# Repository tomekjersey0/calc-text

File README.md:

# CalcText

## What is CalcText?

CalcText is a wireless messaging device enclosed inside a scientific calculator, powered by a single AAA battery. Two units can message each other directly over LoRa, not requiring Wi-Fi, mobile data, or any kind of external infrastructure. The idea came to me from wanting to message a friend who sat far away from me in my maths class without using my phone or shouting. Despite being a little odd, the idea stuck with me.

*CalcText Rev A mainboard 3D render.*

## How it works

CalcText replaces all of the internal calculator electronics, including the PCB and LCD screen, whilst making use of some of the existing mechanical features.

CalcText makes use of several electronic components.

| Part | Purpose |
| --- | --- |
| Wio-E5-LE | MCU and LoRa radio module |
| TPS61299 | Boosts AAA voltage to 3.3 V |
| PCAL9535A | GPIO expander, scans original keypad matrix for input |
| HLCD290TB reflective display | Replacement display for calculator |
| Interposer board | Connects display to mainboard |
| ~90 mm wire antenna | Used for 868 MHz LoRa |

*Original calculator keypad and PCB assembly.*

CalcText makes use of an existing elastomeric keypad that was part of the original calculator. It gives the user a way to interact with the contacts on the PCB. The old contact pattern is therefore replicated on the replacement PCB.

*Rev A mainboard PCB layout.*

A direct FPC connection isn't viable from the reflective display to the mainboard, so an intermediary interposer board is used, to be located on the rear of the display.

*LCD interposer 3D render.*

## Fitting it inside the calculator

The main challenge is getting everything to fit inside the original enclosure.

| Part to fit | Issue | Resolution |
| --- | --- | --- |
| Mainboard | There are mounting holes, thickness, and outline constraints | Produced acrylic fit test using school equipment and measured original PCB thickness with calipers |
| Display | Larger footprint and thinner than original | Sections of the enclosure can be removed, and PORON foam can secure it |
| Interposer | Unknown FPC landing position due to bend once display is installed | Order screen first and design interposer size based on measured landing position |
| Antenna | Needs sufficient distance from metal and components to ensure good transmission quality | Keep antenna routed down long edge through visible gap, allow it to exit the PCB as far from the display and battery as possible |

*Acrylic mainboard fit test inside the calculator enclosure + Location of battery.*

## Current status

| Element | Status |
| --- | --- |
| Mainboard schematic | Complete |
| Mainboard layout | Complete |
| Interposer schematic | Complete |
| Interposer layout | Pending display measurements |
| BOM | Complete |
| Physical build | Pending components |
| Funding | Pending review |

## Next steps

1. Submit project for review
2. Order all currently finalised parts
3. Take necessary measurements
4. Complete and order interposer
5. Fully assemble 2 CalcTexts
6. Write firmware
7. Test messaging
8. Tune antenna if necessary
9. Project complete

## BOM

The full BOM can be found in [`bom.csv`](bom.csv).
This BOM covers *two* individual CalcText units.

## Credits

This project was enabled by [Hack Club, Macondo](https://macondo.hackclub.com).

You can access the project's full development journal [here](https://macondo.hackclub.com/projects/16515).

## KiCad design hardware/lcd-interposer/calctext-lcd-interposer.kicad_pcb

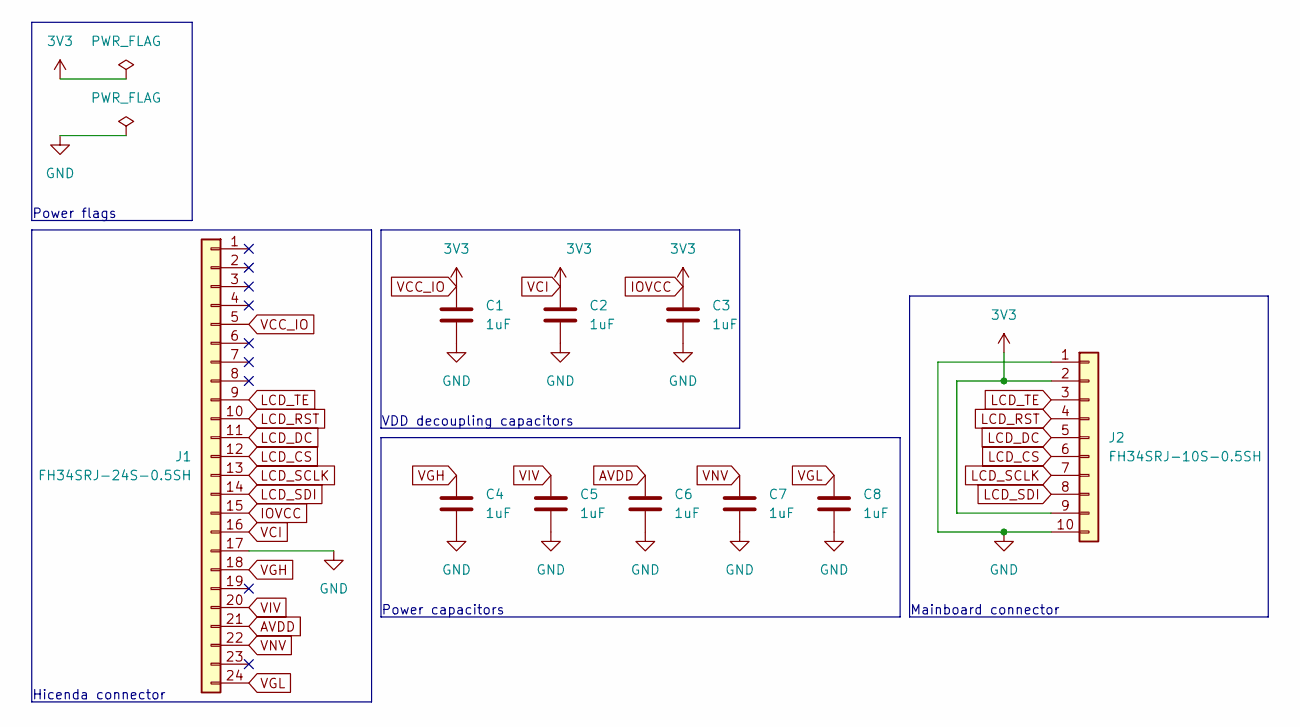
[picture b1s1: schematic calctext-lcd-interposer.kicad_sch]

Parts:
C1, C2, C3, C4, C5, C6, C7, C8: 1uF; C_0402_1005Metric; MPN C1005X5R1E105K050BC
J1: FH34SRJ-24S-0.5SH; Hirose_FH34SRJ-24S-0.5SH; MPN FH34SRJ-24S-0.5SH(99)
J2: FH34SRJ-10S-0.5SH; Hirose_FH34SRJ-10S-0.5SH; MPN FH34SRJ-10S-0.5SH(99)

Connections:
AVDD: C6.2, J1.21
GND: C1.1, C2.1, C3.1, C4.1, C5.1, C6.1, C7.1, C8.1, J1.17, J2.1 (3.3V), J2.10 (GND_P)
IOVCC: C1.2, C2.2, C3.2, J1.5, J1.15, J1.16, J2.2 (GND_L), J2.9 (VBIAS)
LCD_CS: J1.12, J2.6 (DC)
LCD_DC: J1.11, J2.5 (NSS)
LCD_RST: J1.10, J2.4 (MOSI)
LCD_SCLK: J1.13, J2.7 (RESET)
LCD_SDI: J1.14, J2.8 (PWM)
LCD_TE: J1.9, J2.3 (SCK)
VGH: C4.2, J1.18
VGL: C8.2, J1.24
VIV: C5.2, J1.20
VNV: C7.2, J1.22

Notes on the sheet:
VDD decoupling capacitors
Hicenda connector
Power capacitors
Mainboard connector
Power flags

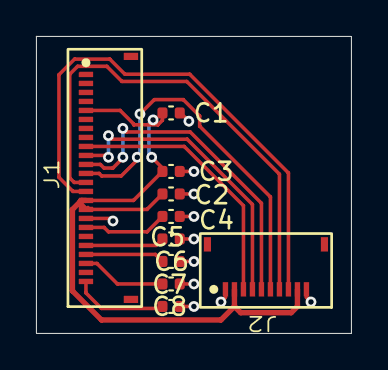
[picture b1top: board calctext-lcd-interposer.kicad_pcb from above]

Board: 2 copper layers, 17.5 x 16.5 mm, 10 parts (0 on the bottom side), 13 nets.

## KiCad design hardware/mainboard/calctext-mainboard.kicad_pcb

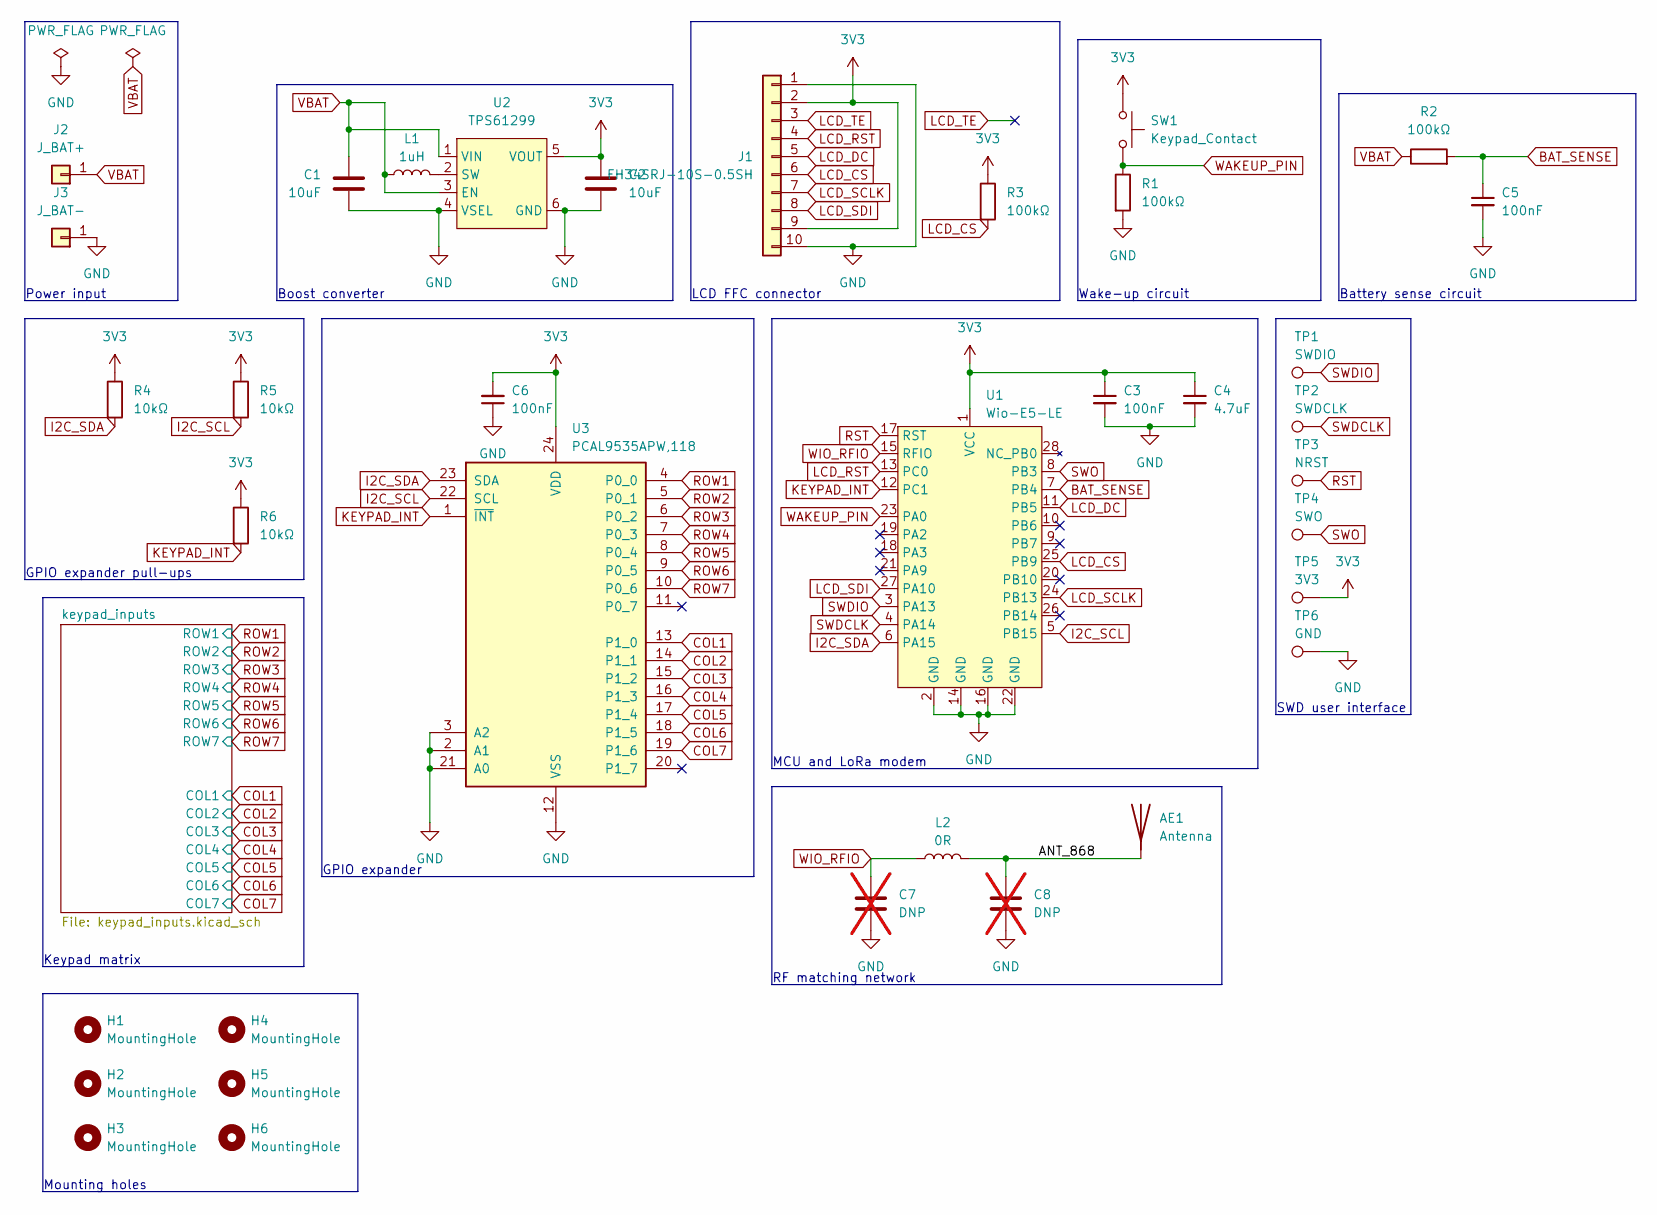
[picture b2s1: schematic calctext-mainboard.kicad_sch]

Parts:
AE1: Antenna; Wire_Antenna_PTH
C1, C2: 10uF; C_0805_2012Metric_Pad1.18x1.45mm_HandSolder; MPN CL21B106KOQNNNE
C3, C5, C6: 100nF; C_0603_1608Metric_Pad1.08x0.95mm_HandSolder; MPN C0603C104K5RACTU
C4: 4.7uF; C_0603_1608Metric_Pad1.08x0.95mm_HandSolder; MPN CL10B475KQ8NNNC
C7, C8: DNP; C_0402_1005Metric; not fitted
H1, H2, H3, H4, H5, H6: MountingHole; MountingHole_4.3mm_M4
J1: FH34SRJ-10S-0.5SH; Hirose_FH34SRJ-10S-0.5SH; MPN FH34SRJ-10S-0.5SH(99)
J2: J_BAT+; Wire_Solder_PTH
J3: J_BAT-; Wire_Solder_PTH
L1: 1uH; L_INPAQ_WIP252010; MPN WIP252010P-1R0ML
L2: 0R; L_0402_1005Metric; MPN RC0402JR-070RL
R1, R2, R3: 100kΩ; R_0603_1608Metric_Pad0.98x0.95mm_HandSolder; MPN RMCF0603FT100K
R4, R5, R6: 10kΩ; R_0603_1608Metric_Pad0.98x0.95mm_HandSolder; MPN RC0603FR-0710KL
SW1: Keypad_Contact
TP1: SWDIO; TestPoint_Pad_D2.0mm
TP2: SWDCLK; TestPoint_Pad_D2.0mm
TP3: NRST; TestPoint_Pad_D2.0mm
TP4: SWO; TestPoint_Pad_D2.0mm
TP5: 3V3; TestPoint_Pad_D2.0mm
TP6: GND; TestPoint_Pad_D2.0mm
U1: Wio-E5-LE; MPN Wio-E5-LE
U2: TPS61299; Texas_R-PDSO-N6_DRL-6; MPN TPS61299DRLR
U3: PCAL9535APW,118; TSSOP-24_4.4x7.8mm_P0.65mm; MPN PCAL9535APW,118

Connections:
3V3: C2.1, C3.1, C4.1, C6.2, J1.2 (GND_L), J1.9 (VBIAS), R3.1, R4.1, R5.1, R6.1, SW1.1, TP5.1, U1.1 (VCC), U2.5 (VOUT), U3.24 (VDD)
/ANT_868: AE1.1 (A), C8.1, L2.2
BAT_SENSE: C5.1, R2.2, U1.7 (PB4)
COL1: U3.13 (P1_0); also elsewhere on the board
COL2: U3.14 (P1_1); also elsewhere on the board
COL3: U3.15 (P1_2); also elsewhere on the board
COL4: U3.16 (P1_3); also elsewhere on the board
COL5: U3.17 (P1_4); also elsewhere on the board
COL6: U3.18 (P1_5); also elsewhere on the board
COL7: U3.19 (P1_6); also elsewhere on the board
GND: C1.2, C2.2, C3.2, C4.2, C5.2, C6.1, C7.2, C8.2, J1.1 (3.3V), J1.10 (GND_P), J3.1, R1.2, TP6.1, U1.2 (GND), U1.14 (GND), U1.16 (GND), U1.22 (GND), U2.4 (VSEL), U2.6 (GND), U3.2 (A1), U3.3 (A2), U3.12 (VSS), U3.21 (A0)
I2C_SCL: R5.2, U1.5 (PB15), U3.22 (SCL)
I2C_SDA: R4.2, U1.6 (PA15), U3.23 (SDA)
KEYPAD_INT: R6.2, U1.12 (PC1), U3.1 (~INT)
LCD_CS: J1.6 (DC), R3.2, U1.25 (PB9)
LCD_DC: J1.5 (NSS), U1.11 (PB5)
LCD_RST: J1.4 (MOSI), U1.13 (PC0)
LCD_SCLK: J1.7 (RESET), U1.24 (PB13)
LCD_SDI: J1.8 (PWM), U1.27 (PA10)
LCD_TE: J1.3 (SCK)
unnamed: L1.2, U2.2 (SW)
ROW1: U3.4 (P0_0); also elsewhere on the board
ROW2: U3.5 (P0_1); also elsewhere on the board
ROW3: U3.6 (P0_2); also elsewhere on the board
ROW4: U3.7 (P0_3); also elsewhere on the board
ROW5: U3.8 (P0_4); also elsewhere on the board
ROW6: U3.9 (P0_5); also elsewhere on the board
ROW7: U3.10 (P0_6); also elsewhere on the board
RST: TP3.1, U1.17 (RST)
SWDCLK: TP2.1, U1.4 (PA14)
SWDIO: TP1.1, U1.3 (PA13)
SWO: TP4.1, U1.8 (PB3)
VBAT: C1.1, J2.1, L1.1, R2.1, U2.1 (VIN), U2.3 (EN)
WAKEUP_PIN: R1.1, SW1.2, U1.23 (PA0)
WIO_RFIO: C7.1, L2.1, U1.15 (RFIO)

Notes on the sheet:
Keypad matrix
Wake-up circuit
Power input
GPIO expander pull-ups
Boost converter
MCU and LoRa modem
GPIO expander
LCD FFC connector
SWD user interface
RF matching network
Mounting holes
Battery sense circuit

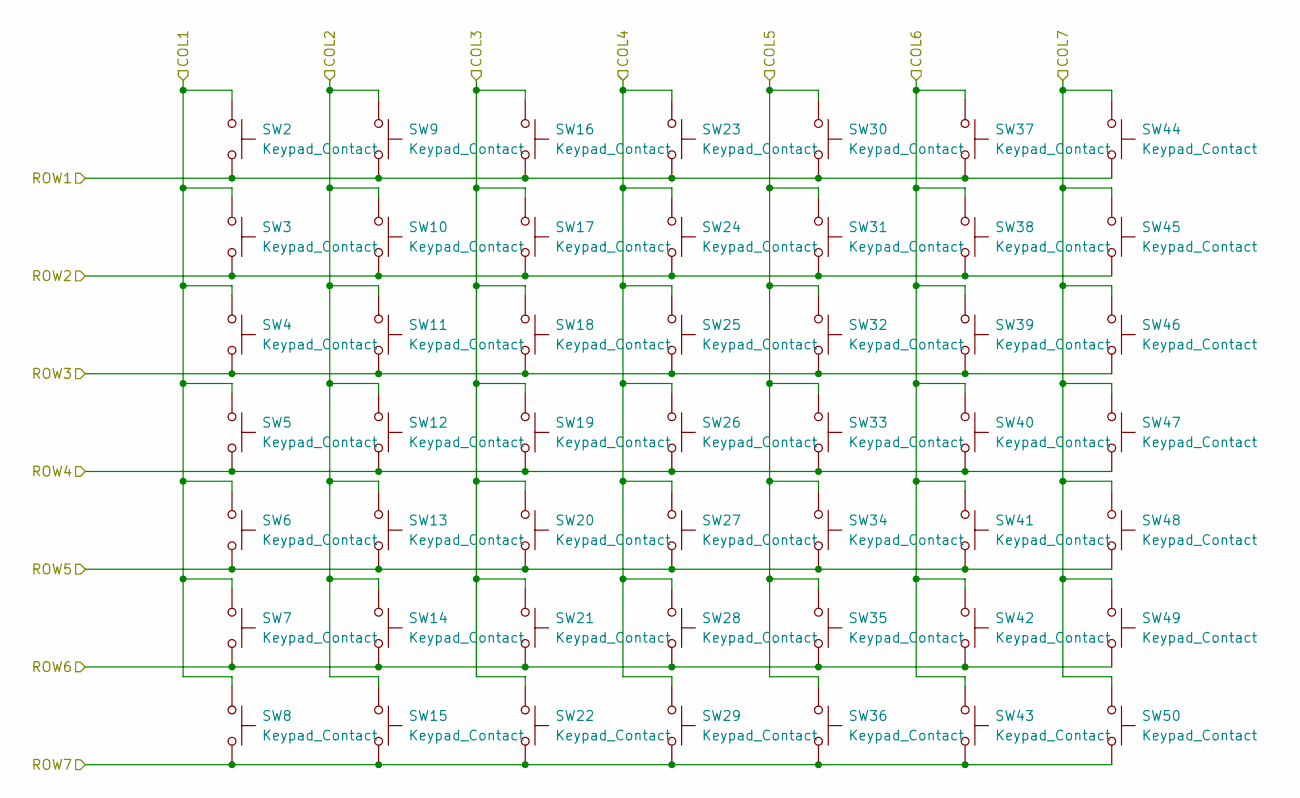
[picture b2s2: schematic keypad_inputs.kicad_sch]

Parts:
SW2, SW3, SW4, SW5, SW6, SW7, SW8, SW9, SW10, SW11, SW12, SW13, SW14, SW15, SW16, SW17, SW18, SW19, SW20, SW21, SW22, SW23, SW24, SW25, SW26, SW27, SW28, SW29, SW30, SW31, SW32, SW33, SW34, SW35, SW36, SW37, SW38, SW39, SW40, SW41, SW42, SW43, SW44, SW45, SW46, SW47, SW48, SW49, SW50: Keypad_Contact

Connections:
COL1: SW2.1, SW3.1, SW4.1, SW5.1, SW6.1, SW7.1, SW8.1; also elsewhere on the board
COL2: SW9.1, SW10.1, SW11.1, SW12.1, SW13.1, SW14.1, SW15.1; also elsewhere on the board
COL3: SW16.1, SW17.1, SW18.1, SW19.1, SW20.1, SW21.1, SW22.1; also elsewhere on the board
COL4: SW23.1, SW24.1, SW25.1, SW26.1, SW27.1, SW28.1, SW29.1; also elsewhere on the board
COL5: SW30.1, SW31.1, SW32.1, SW33.1, SW34.1, SW35.1, SW36.1; also elsewhere on the board
COL6: SW37.1, SW38.1, SW39.1, SW40.1, SW41.1, SW42.1, SW43.1; also elsewhere on the board
COL7: SW44.1, SW45.1, SW46.1, SW47.1, SW48.1, SW49.1, SW50.1; also elsewhere on the board
ROW1: SW2.2, SW9.2, SW16.2, SW23.2, SW30.2, SW37.2, SW44.2; also elsewhere on the board
ROW2: SW3.2, SW10.2, SW17.2, SW24.2, SW31.2, SW38.2, SW45.2; also elsewhere on the board
ROW3: SW4.2, SW11.2, SW18.2, SW25.2, SW32.2, SW39.2, SW46.2; also elsewhere on the board
ROW4: SW5.2, SW12.2, SW19.2, SW26.2, SW33.2, SW40.2, SW47.2; also elsewhere on the board
ROW5: SW6.2, SW13.2, SW20.2, SW27.2, SW34.2, SW41.2, SW48.2; also elsewhere on the board
ROW6: SW7.2, SW14.2, SW21.2, SW28.2, SW35.2, SW42.2, SW49.2; also elsewhere on the board
ROW7: SW8.2, SW15.2, SW22.2, SW29.2, SW36.2, SW43.2, SW50.2; also elsewhere on the board

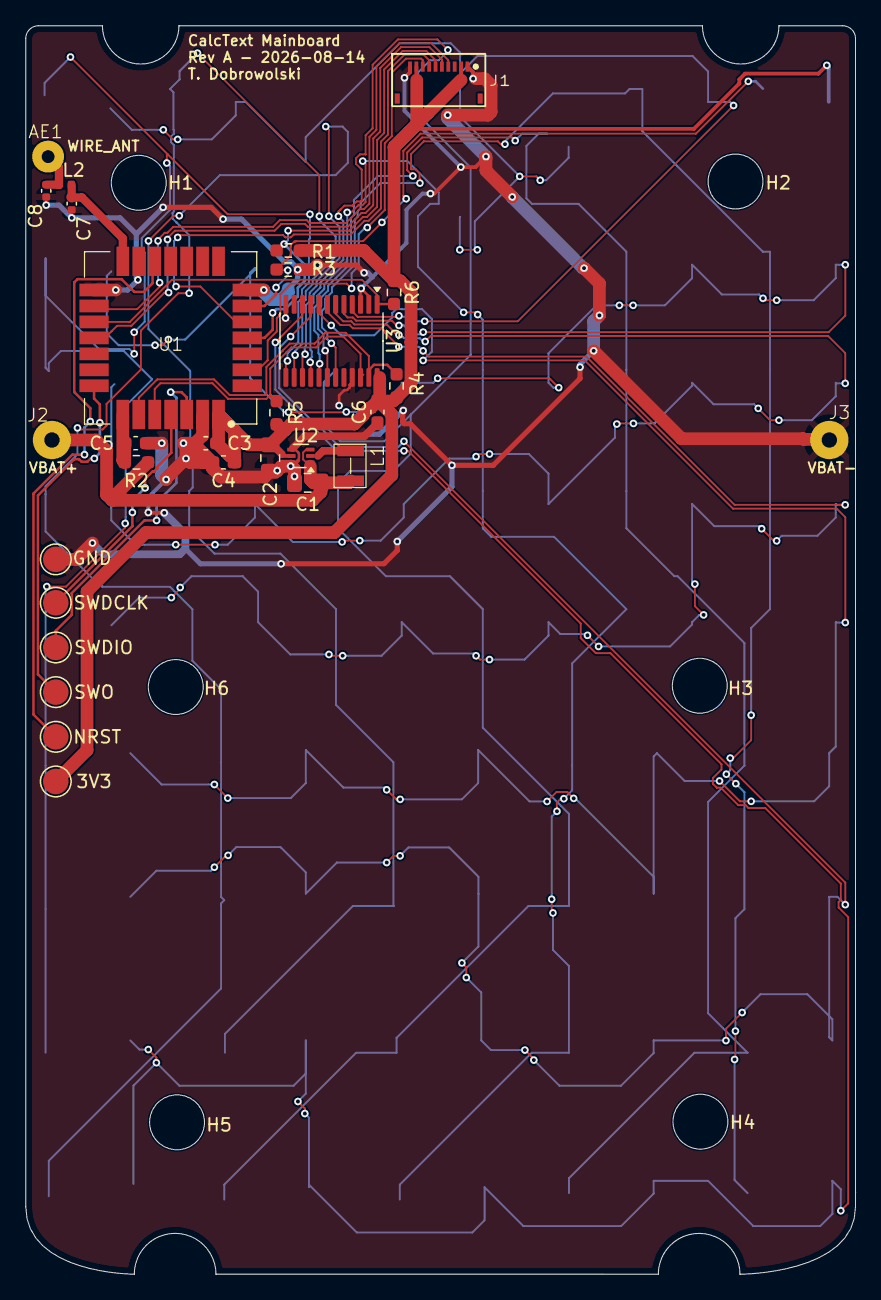
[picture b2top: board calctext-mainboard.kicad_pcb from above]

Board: 4 copper layers, 65.0 x 97.8 mm, 85 parts (0 on the bottom side), 34 nets.

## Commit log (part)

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2026-03-24 fix: move mounting holes
2026-03-24 fix: move bottom holes up 2.7 right 1.0mm
2026-03-24 refactor: remove most of annoying fab marks
2026-03-24 feat: fillet edges of outline
2026-03-24 feat: fillet edges + good holes
2026-03-25 fix: adjust bottom two holes
2026-03-26 refactor: set hole size to 4.3mm
